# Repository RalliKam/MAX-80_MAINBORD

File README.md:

# LOBO MAX-80 · CPU Logic Board

This KiCad 10 project recreates the LOBO MAX-80 mainboard from the original schematics. The board contains the Z80B processor, main memory, serial interfaces, floppy disk controller, and video circuitry.
The work ist NOT finished!!!!

The schematic spans five sheets. The PCB layout contains **228 footprints**. Routing is still pending.

## Technical documentation

- [MAX-80 Technical Reference Manual (PDF)](Tech_Ref_Manual_Updated.pdf)
- [Appendix H – Original Schematics (PDF)](z80_Appendix_H_Schematics_Updated.pdf)
- [CPU logic board component placement diagram](CPU%20LOGIC%20Board.png)

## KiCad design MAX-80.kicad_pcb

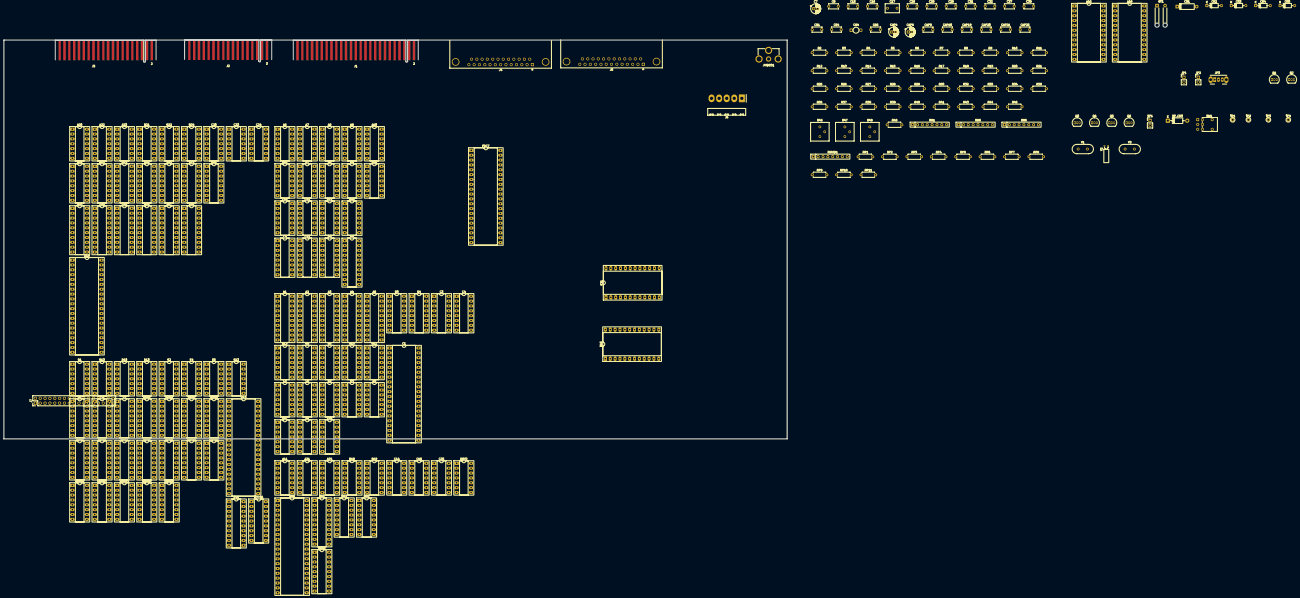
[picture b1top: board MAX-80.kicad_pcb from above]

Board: 2 copper layers, 410.0 x 208.7 mm, 228 parts (0 on the bottom side), 533 nets, no tracks yet.

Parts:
A1: 74LS688; DIP-20_W7.62mm_Socket_LongPads
A2: 74LS273; DIP-20_W7.62mm_Socket_LongPads
A3: 74LS245; DIP-20_W7.62mm_Socket_LongPads
A4, A5: 74LS244; DIP-20_W7.62mm_Socket_LongPads
A6: 74LS14; DIP-14_W7.62mm_Socket_LongPads
A7, A10: 7406; DIP-14_W7.62mm_Socket_LongPads
A8, A9, A12: 7438; DIP-14_W7.62mm_Socket_LongPads
A11, A24: 74LS393; DIP-14_W7.62mm_Socket_LongPads
A13: 74LS04; DIP-14_W7.62mm_Socket_LongPads
A16: SERIAL B; DIP-24_W15.24mm_Socket_LongPads
A18: SERIAL A; DIP-24_W15.24mm_Socket_LongPads
A20: 74LS20; DIP-14_W7.62mm_Socket_LongPads
A21: 74LS00; DIP-14_W7.62mm_Socket_LongPads
A22, A23: 74LS02; DIP-14_W7.62mm_Socket_LongPads
B1, B22: 74LS11; DIP-14_W7.62mm_Socket_LongPads
B2: 74LS157; DIP-16_W7.62mm_Socket_LongPads
B3: 74S139; DIP-16_W7.62mm_Socket_LongPads
B4: 74LS138; DIP-16_W7.62mm_Socket_LongPads
B5: 74S32; DIP-14_W7.62mm_Socket_LongPads
B6, B24: 74LS32; DIP-14_W7.62mm_Socket_LongPads
B7, B11: 74LS00; DIP-14_W7.62mm_Socket_LongPads
B8: 74LS393; DIP-14_W7.62mm_Socket_LongPads
B9, B13, B21: 74LS04; DIP-14_W7.62mm_Socket_LongPads
B10: 74LS02; DIP-14_W7.62mm_Socket_LongPads
B12: 74LS74; DIP-14_W7.62mm_Socket_LongPads
B14, B25: 74LS109; DIP-16_W7.62mm_Socket_LongPads
B15: 74LS244; DIP-20_W7.62mm_Socket_LongPads
B16: Z80 SIO/2; DIP-40_W15.24mm_Socket_LongPads
B18, B19: MC1489; DIP-14_W7.62mm_Socket_LongPads
B20: 74LS161; DIP-16_W7.62mm_Socket_LongPads
B23: 74LS273; DIP-20_W7.62mm_Socket_LongPads
BRG1: COM8116; DIP-18_W7.62mm_Socket_LongPads
BT1: 3,6 V NiCd; SolderWire-0.25sqmm_1x02_P4.2mm_D0.65mm_OD1.7mm_Relief
C1: Z80B; DIP-40_W15.24mm_Socket_LongPads
C3: 74S139; DIP-16_W7.62mm_Socket_LongPads
C4: 74LS138; DIP-16_W7.62mm_Socket_LongPads
C5: 74S32; DIP-14_W7.62mm_Socket_LongPads
C6: 74LS30; DIP-14_W7.62mm_Socket_LongPads
C7: 10 µF; CP_Radial_D5.0mm_P2.00mm
C8: 680NF; C_Disc_D5.0mm_W2.5mm_P5.00mm
C9: 74LS175; DIP-16_W7.62mm_Socket_LongPads
C10: 74LS132; DIP-14_W7.62mm_Socket_LongPads
C11, C23: 74LS00; DIP-14_W7.62mm_Socket_LongPads
C12: 74LS629; DIP-16_W7.62mm_Socket_LongPads
C14: 74LS393; DIP-14_W7.62mm_Socket_LongPads
C15, C16, C66: 100nF; C_Disc_D5.0mm_W2.5mm_P5.00mm
C17: 1 µF; C_Rect_L7.2mm_W4.5mm_P5.00mm
C19: MC1488; DIP-14_W7.62mm_Socket_LongPads
C20: 74LS02; DIP-14_W7.62mm_Socket_LongPads
C21, C22: 74LS273; DIP-20_W7.62mm_Socket_LongPads
C24: 74LS08; DIP-14_W7.62mm_Socket_LongPads
C25: 74LS04; DIP-14_W7.62mm_Socket_LongPads
C26: 200nF; C_Disc_D5.0mm_W2.5mm_P5.00mm
C28, C29: 0,01 µF; C_Disc_D5.0mm_W2.5mm_P5.00mm
C31, C32: 0,001 µF; C_Disc_D5.0mm_W2.5mm_P5.00mm
C37: 68 nF; C_Disc_D5.0mm_W2.5mm_P5.00mm
C38: 39 nF; C_Disc_D5.0mm_W2.5mm_P5.00mm
C51: 20 pF; C_Disc_D5.0mm_W2.5mm_P5.00mm
C54: 200nf; C_Disc_D5.0mm_W2.5mm_P5.00mm
C64: 5–35 pF; C_Trimmer_GKX35011_P5.00mm
CAP4: 10 µF; CP_Radial_D5.0mm_P2.00mm
CAP6: 1 µF; CP_Radial_D5.0mm_P2.00mm
CAP9: 200nF; C_Disc_D5.0mm_W2.5mm_P5.00mm
CAP10, CAP20: 390; C_Disc_D5.0mm_W2.5mm_P5.00mm
CAP19: 180; C_Disc_D5.0mm_W2.5mm_P5.00mm
CAP21: 200 pF; C_Disc_D5.0mm_W2.5mm_P5.00mm
CAP25: 430; C_Disc_D5.0mm_W2.5mm_P5.00mm
CR1: 1N34A; D_DO-7_P10.16mm_Horizontal
CR2, CR3, CR4, CR5: 1N4148; D_DO-35_SOD27_P7.62mm_Horizontal
D3: 74LS11; DIP-14_W7.62mm_Socket_LongPads
D4: 74LS20; DIP-14_W7.62mm_Socket_LongPads
D5: 74LS04; DIP-14_W7.62mm_Socket_LongPads
D6: 74LS273; DIP-20_W7.62mm_Socket_LongPads
D9: 74LS123; DIP-16_W7.62mm_Socket_LongPads
D10, D11, D12: 74LS74; DIP-14_W7.62mm_Socket_LongPads
D13: 74LS02; DIP-14_W7.62mm_Socket_LongPads
D14: Z80 PIO; DIP-40_W15.24mm_Socket_LongPads
D16: 6116; DIP-24_W15.24mm_Socket_LongPads
D17: 74LS08; DIP-14_W7.62mm_Socket_LongPads
D18: HD46505; DIP-40_W15.24mm_Socket_LongPads
D20: 74LS245; DIP-20_W7.62mm_Socket_LongPads
D23, D24, D25: 74LS157; DIP-16_W7.62mm_Socket_LongPads
DRV2: MC1488; DIP-14_W7.62mm_Socket_LongPads
E1, E13: 74LS32; DIP-14_W7.62mm_Socket_LongPads
E2, E16: 74LS74; DIP-14_W7.62mm_Socket_LongPads
E4: 74LS393; DIP-14_W7.62mm_Socket_LongPads
E5: 74LS00; DIP-14_W7.62mm_Socket_LongPads
E12: 74S472; DIP-20_W7.62mm_Socket_LongPads
E17: 74LS323; DIP-20_W7.62mm_Socket_LongPads
E20: 74LS245; DIP-20_W7.62mm_Socket_LongPads
E21: 6116; DIP-24_W15.24mm_Socket_LongPads
E23, E24, E25: 74LS157; DIP-16_W7.62mm_Socket_LongPads
F4, F5: 74LS157; DIP-16_W7.62mm_Socket_LongPads
FDC7: 8866; DIP-40_W15.24mm_Socket_LongPads
J1: Floppy 8 Zoll; Floppy_Shugart_50Pin_P2.54mm_Key4-6
J2: Floppy 5¼ Zoll; Floppy_Shugart_34Pin_P2.54mm_Key4-6
J3: Systembus; Expansion_40Pin_P2.54mm_Key4-6
J4: RS-232 A; DSUB-25_Pins_Horizontal_P2.77x2.84mm_EdgePinOffset9.90mm_Ho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
J5: RS-232 B; DSUB-25_Pins_Horizontal_P2.77x2.84mm_EdgePinOffset9.90mm_Ho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
J6: Netzteileingang (A/25); Molex_KK-396_A-41792-0005_1x05_P3.96mm_Horizontal
J7: Keyboard Interface; PinHeader_2x17_P2.54mm_Vertical
JP1: BUSRQ; PinHeader_1x02_P2.54mm_Vertical
JP2: HALT; PinHeader_1x02_P2.54mm_Vertical
JP3: SIDE / DS4; SW_Slide_SPDT_Angled_CK_OS102011MA1Q
JVIDEO1: Video · Cinch; CUI_RCJ-01X_MAX80
Q1, Q6: 2N3906; TO-92_Inline
Q2, Q3, Q4, Q5: 2N3904; TO-92_Inline
R2, R38: 5,6 kΩ; R_Axial_DIN0207_L6.3mm_D2.5mm_P7.62mm_Horizontal
R3, R14: 2,7 kΩ; R_Axial_DIN0207_L6.3mm_D2.5mm_P7.62mm_Horizontal
R4, R6, R25: 10 kΩ; R_Axial_DIN0207_L6.3mm_D2.5mm_P7.62mm_Horizontal
R5, R16, R18, R41, R43, R49: 1 kΩ; R_Axial_DIN0207_L6.3mm_D2.5mm_P7.62mm_Horizontal
R7, R8, R9, R10, R11, R12: 150 Ω; R_Axial_DIN0207_L6.3mm_D2.5mm_P7.62mm_Horizontal
R13: 1,8 kΩ; R_Axial_DIN0207_L6.3mm_D2.5mm_P7.62mm_Horizontal
R15: 75 Ω; R_Axial_DIN0207_L6.3mm_D2.5mm_P7.62mm_Horizontal
R17: 2,2 kΩ; R_Axial_DIN0207_L6.3mm_D2.5mm_P7.62mm_Horizontal
R19, R21, R32, R33, R36: 330 Ω; R_Axial_DIN0207_L6.3mm_D2.5mm_P7.62mm_Horizontal
R20: 470 Ω; R_Axial_DIN0207_L6.3mm_D2.5mm_P7.62mm_Horizontal
R26: 15 kΩ; R_Axial_DIN0207_L6.3mm_D2.5mm_P7.62mm_Horizontal
R27: 47 kΩ; R_Axial_DIN0207_L6.3mm_D2.5mm_P7.62mm_Horizontal
R28: 68 kΩ; R_Axial_DIN0207_L6.3mm_D2.5mm_P7.62mm_Horizontal
R29, R30: 56 Ω; R_Axial_DIN0207_L6.3mm_D2.5mm_P7.62mm_Horizontal
R34, R37: 4,7 kΩ; R_Axial_DIN0207_L6.3mm_D2.5mm_P7.62mm_Horizontal
R35: 3 kΩ; R_Axial_DIN0207_L6.3mm_D2.5mm_P7.62mm_Horizontal
R39, R40, R44: 200 Ω; R_Axial_DIN0207_L6.3mm_D2.5mm_P7.62mm_Horizontal
R45: 22 Ω; R_Axial_DIN0207_L6.3mm_D2.5mm_P7.62mm_Horizontal
R46, R47, R48: 5 kΩ; Potentiometer_Bourns_3386P_Vertical
RAM1, RAM2, RAM3, RAM4, RAM5, RAM6, RAM7, RAM8, RAM9, RAM10, RAM11, RAM12, RAM13, RAM14, RAM15, RAM16: 4164; DIP-16_W7.62mm_Socket_LongPads
RN1: 2,7 kΩ; R_Array_SIP8
RN5: 1 kΩ; R_Array_SIP8
RN6: 150 Ω; R_Array_SIP8
RNVID1: 2,7 kΩ; R_Array_SIP8
RP1, RP2, RP3, RP4, RP5, RP6, RP7, RP8, RP9, RP10, RP11: 10 kΩ; R_Axial_DIN0207_L6.3mm_D2.5mm_P7.62mm_Horizontal
RTC16: MSM5832; DIP-18_W7.62mm_Socket_LongPads
SP1: Lautsprecher; PinHeader_1x02_P2.54mm_Vertical
SP_CR3: 1N4003; D_DO-41_SOD81_P10.16mm_Horizontal
SW1: CLOCK SET; Clock_Set_800UDP8P1A1M6
TP1: TP; TestPoint_THTPad_D2.0mm_Drill1.0mm
TP2, TP3, TP4: Prüfpunkt; TestPoint_THTPad_D2.0mm_Drill1.0mm
Y1: 8,00 MHz; Crystal_HC49-U_Vertical
Y2: 32,768 kHz; Crystal_C26-LF_D2.1mm_L6.5mm_Horizontal
Y3: 15,2 MHz; Crystal_HC49-U_Vertical

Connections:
5SEC: A7.11, B7.1, B7.8, B7.12, B15.6 (1A3)
500KC: A11.8 (D), C14.1 (CLK)
+5V: A1.20 (VCC), A2.20 (VCC), A3.20 (VCC), A4.20 (VCC), A5.20 (VCC), A6.14 (+5V), A7.14 (+5V), A8.14 (+5V), A9.14 (+5V), A10.14 (+5V), A11.14 (+5V), A12.14 (+5V), A13.14 (VCC), A20.14 (+5V), A21.14 (+5V), A22.14 (+5V), A23.14 (+5V), A24.14 (+5V), B1.14 (+5V), B2.16 (+5V), B3.16 (VCC), B4.16 (VCC), B5.14 (VCC), B6.14 (VCC), B7.14 (+5V), B8.14 (+5V), B9.14 (+5V), B10.14 (VCC), B11.14 (VCC), B12.14 (+5V), B13.14 (VCC), B14.16 (+5V), B15.20 (+5V), B16.6 (IEI), B16.8 (~M1), B16.9 (VCC), B18.14 (+5V), B19.14 (+5V), B20.16 (+5V), B21.14 (+5V), B22.14 (+5V), B23.20 (+5V), B24.14 (+5V), B25.16 (+5V), BRG1.2 (VCC), C1.11 (VCC), C3.16 (VCC), C4.16 (VCC), C5.14 (VCC), C6.14 (VCC), C9.16 (+5V), C10.14 (+5V), C11.14 (+5V), C12.3 (RNG), C12.14 (RNG), C12.15 (+5V), C12.16 (+5V), C14.14 (+5V), C17.1, C20.14 (+5V), C21.20 (+5V), C22.20 (+5V), C23.14 (+5V), C24.14 (+5V), C25.14 (+5V), D3.14 (VCC), D4.14 (VCC), D5.14 (VCC), D6.20 (+5V), D9.16 (+5V), D10.14 (VCC), D11.14 (+5V), D12.14 (+5V), D13.14 (VCC), D14.26 (VCC), D14.37 (~M1), D16.24 (VCC), D17.14 (VCC), D18.2 (~RES), D18.20 (VCC), D20.20 (+5V), D23.16 (+5V), D24.16 (+5V), D25.16 (+5V), E1.14 (VCC), E2.14 (+5V), E4.14 (+5V), E5.14 (+5V), E12.20 (+5V), E13.14 (VCC), E16.14 (VCC), E17.20 (+5V), E20.20 (+5V), E21.24 (VCC), E23.16 (+5V), E24.16 (+5V), E25.16 (+5V), F4.16 (+5V), F5.16 (+5V), FDC7.21 (VCC), J6.1, J6.5, J7.28, J7.29, Q4.3, Q5.3, R2.1, R3.1, R4.1, R14.1, R36.2, R38.2, R41.1, R45.1, R46.3, R47.1, R48.1, R49.1, RAM1.8 (VCC), RAM2.8 (VCC), RAM3.8 (VCC), RAM4.8 (VCC), RAM5.8 (VCC), RAM6.8 (VCC), RAM7.8 (VCC), RAM8.8 (VCC), RAM9.8 (VCC), RAM10.8 (VCC), RAM11.8 (VCC), RAM12.8 (VCC), RAM13.8 (VCC), RAM14.8 (VCC), RAM15.8 (VCC), RAM16.8 (VCC), RN1.1, RN5.1, RN6.1, RNVID1.1, RP1.1, RP2.1, RP3.1, RP4.1, RP5.1, RP6.1, RP7.1, RP8.1, RP9.1, RP10.1, RP11.1, SP1.1, SP_CR3.1
+12V: BRG1.9 (VDD), C19.14 (VCC), DRV2.14 (VCC), J6.3, R6.1, R8.2, R10.2
-12V: C19.1 (VEE), DRV2.1 (VEE), J6.4, R9.2, R11.2
/1 · CPU und Systembus/J3_18: A4.3 (2Y4), J3.18
/1 · CPU und Systembus/XA0: A5.3 (2Y4), J3.26
/1 · CPU und Systembus/XA1: A5.5 (2Y3), J3.28
/1 · CPU und Systembus/XA2: A5.7 (2Y2), J3.39
/1 · CPU und Systembus/XA3: A5.9 (2Y1), J3.33
/1 · CPU und Systembus/XA4: A5.12 (1Y4), J3.32
/1 · CPU und Systembus/XA5: A5.14 (1Y3), J3.36
/1 · CPU und Systembus/XA6: A5.16 (1Y2), J3.37
/1 · CPU und Systembus/XA7: A5.18 (1Y1), J3.35
/1 · CPU und Systembus/XD0: A3.11 (B8), J3.29
/1 · CPU und Systembus/XD1: A3.12 (B7), J3.21
/1 · CPU und Systembus/XD2: A3.13 (B6), J3.31
/1 · CPU und Systembus/XD3: A3.14 (B5), J3.25
/1 · CPU und Systembus/XD4: A3.15 (B4), J3.17
/1 · CPU und Systembus/XD5: A3.16 (B3), J3.27
/1 · CPU und Systembus/XD6: A3.17 (B2), J3.23
/1 · CPU und Systembus/XD7: A3.18 (B1), J3.19
/1 · CPU und Systembus/XΦZ: A4.5 (2Y3), J3.6
/1 · CPU und Systembus/~WAIT: E1.12, J3.34, RN1.8
/1 · CPU und Systembus/~XINTAK: A4.7 (2Y2), CR1.1, J3.13
/1 · CPU und Systembus/~XINT: D3.9, J3.22, RN1.7
/1 · CPU und Systembus/~XIN: A4.14 (1Y3), J3.20
/1 · CPU und Systembus/~XIORQ: A4.12 (1Y4), J3.10
/1 · CPU und Systembus/~XM1: A4.9 (2Y1), J3.9
/1 · CPU und Systembus/~XNMI: E1.1, J3.24, RN1.4
/1 · CPU und Systembus/~XOUT: A4.16 (1Y2), J3.11
/1 · CPU und Systembus/~XSYSRES: A4.18 (1Y1), J3.1
/4 · Floppycontroller und Laufwerke/1M: A11.9 (C), B11.12, B12.3 (CLK)
/4 · Floppycontroller und Laufwerke/2M: A11.10 (B), B11.9
A0: A5.17 (2A4), C1.30 (A0), D14.5 (C/~D), D18.24 (RS), D23.11 (A2), E12.1 (A0), E23.14 (A3), F5.2 (1A), FDC7.5 (A0), J7.2
A1: A5.15 (2A3), C1.31 (A1), D14.6 (B/~A), D23.14 (A3), E12.2, E23.11 (A2), F5.5 (2A), FDC7.6 (A1), J7.3
A2: A5.13 (2A2), B4.1 (A), C1.32 (A2), C3.14 (A), C4.1 (A), D24.2 (A0), E12.3, E23.5 (A1), F5.11 (3A), J7.4
A3: A5.11 (2A1), B4.2 (B), C1.33 (A3), C3.13 (B), C4.2 (B), D24.5 (A1), E12.4, E24.14 (A3), F5.14 (4A), J7.5
A4: A5.8 (1A4), B4.3 (C), C1.34 (A4), C4.3 (C), D4.13, D24.11 (A2), E12.5, E24.11 (A2), F4.2 (1A), J7.6
A5: A5.6 (1A3), B10.5, C1.35 (A5), D4.5, D24.14 (A3), E12.16, E24.5 (A1), F4.5 (2A), J7.7
A6: A5.4 (1A2), C1.36 (A6), D4.4, D4.10, D25.2 (A0), E12.17, E24.2 (A0), F4.11 (3A), J7.8
A7: A5.2 (1A1), C1.37 (A7), D4.1, D4.2, D4.9, D25.5 (A1), E5.12, E12.18, E25.14 (A3), J7.9
A8: B3.14 (A), C1.38 (A8), D25.11 (A2), E12.19 (A8), E25.11 (A2), F5.3 (1B)
A9: B3.13 (B), C1.39 (A9), E25.5 (A1), F5.6 (2B)
A10: B3.2 (A), C1.40 (A10), C25.5, F5.10 (3B)
A11: B3.3 (B), C1.1 (A11), F5.13 (4B)
A12: A1.11 (P4), C1.2 (A12), F4.3 (1B)
A13: A1.13 (P5), C1.3 (A13), F4.6 (2B)
A14: A1.15 (P6), C1.4 (A14), F4.10 (3B)
A15: A1.17 (P7), B2.1 (SEL), C1.5 (A15)
BLOCK: C6.8, E1.5
D0: A2.18 (D7), A3.9 (A8), B16.40 (D0), BRG1.4 (D0B), BRG1.16 (D0A), C1.14 (D0), CR1.2, D6.3 (D0), D14.19 (D0), D18.33 (D0), D20.9 (A8), E12.6 (D0), E20.2 (A1), FDC7.7 (DAL0), J7.11, RAM8.2 (DI), RAM8.14 (DO), RAM16.2 (DI), RAM16.14 (DO)
D1: A2.17 (D6), A3.8 (A7), B16.1 (D1), BRG1.5 (D1B), BRG1.15 (D1A), C1.15 (D1), D6.18 (D7), D14.20, D18.32 (D1), D20.8 (A7), E12.7, E20.3 (A2), FDC7.8 (DAL1), J7.12, RAM7.2 (DI), RAM7.14 (DO), RAM15.2 (DI), RAM15.14 (DO), RNVID1.7
D2: A2.14 (D5), A3.7 (A6), B16.39 (D2), BRG1.6 (D2B), BRG1.14 (D2A), C1.12 (D2), D6.4 (D1), D13.3, D14.1, D18.31 (D2), D20.7 (A6), E12.8, E20.4 (A3), FDC7.9 (DAL2), J7.13, RAM6.2 (DI), RAM6.14 (DO), RAM14.2 (DI), RAM14.14 (DO), RNVID1.6
D3: A2.13 (D4), A3.6 (A5), B16.2 (D3), BRG1.7 (D3B), BRG1.13 (D3A), C1.8 (D3), D6.17 (D6), D14.40, D18.30 (D3), D20.6 (A5), E12.9, E20.5 (A4), FDC7.10 (DAL3), J7.14, RAM5.2 (DI), RAM5.14 (DO), RAM13.2 (DI), RAM13.14 (DO), RNVID1.5
D4: A2.8 (D3), A3.5 (A4), B15.9 (2Y1), B15.18 (1Y1), B16.38 (D4), C1.7 (D4), D6.7 (D2), D14.39, D18.29 (D4), D20.5 (A4), E12.11, E20.6 (A5), FDC7.11 (DAL4), J7.15, RAM4.2 (DI), RAM4.14 (DO), RAM12.2 (DI), RAM12.14 (DO), RNVID1.4
D5: A2.7 (D2), A3.4 (A3), B15.7 (2Y2), B15.16 (1Y2), B16.3 (D5), C1.9 (D5), D6.14 (D5), D14.38, D18.28 (D5), D20.4 (A3), E12.12, E20.7 (A6), FDC7.12 (DAL5), J7.16, RAM3.2 (DI), RAM3.14 (DO), RAM11.2 (DI), RAM11.14 (DO), RNVID1.3
D6: A2.4 (D1), A3.3 (A2), B15.5 (2Y3), B15.14 (1Y3), B16.37 (D6), C1.10 (D6), D6.8 (D3), D14.3, D18.27 (D6), D20.3 (A2), E12.13, E20.8 (A7), FDC7.13 (DAL6), J7.17, RAM2.2 (DI), RAM2.14 (DO), RAM10.2 (DI), RAM10.14 (DO), RNVID1.2
D7: A2.3 (D0), A3.2 (A1), B15.3 (2Y4), B15.12 (1Y4), B16.4 (D7), C1.13 (D7), D6.13 (D4), D14.2 (D7), D18.26 (D7), D20.2 (A1), D23.5 (A1), E12.14 (D7), E20.9 (A8), FDC7.14 (DAL7), J7.18, RAM1.2 (DI), RAM1.14 (DO), RAM9.2 (DI), RAM9.14 (DO), RNVID1.8
DNM: B7.4, D6.12 (Q4), E1.2
DRQ: E13.13, FDC7.38 (DRQ), J7.19
DSPTMG: B15.4 (1A2), C21.18 (D7), D18.18 (DISPTMG)
GND: A1.10 (GND), A2.10 (GND), A3.10 (GND), A4.1 (~1G), A4.10 (GND), A4.19 (~2G), A5.1 (~1G), A5.10 (GND), A5.19 (~2G), A6.7 (GND), A7.7 (GND), A8.7 (GND), A9.7 (GND), A10.7 (GND), A11.2 (CLR), A11.7 (GND), A11.12 (CLR), A12.7 (GND), A13.7 (GND), A20.7 (GND), A21.7 (GND), A22.7 (GND), A23.7 (GND), A24.7 (GND), B1.7 (GND), B2.8 (GND), B2.15 (~EN), B3.8 (GND), B4.8 (GND), B5.7 (GND), B6.7 (GND), B7.7 (GND), B8.7 (GND), B9.7 (GND), B10.7 (GND), B11.7 (GND), B12.7 (GND), B13.7 (GND), B14.2 (J), B14.8 (GND), B14.13 (~K), B15.10 (GND), B16.31 (VSS), B16.35 (~CE), B18.7 (GND), B19.7 (GND), B20.3 (A), B20.4 (B), B20.5 (C), B20.8 (GND), B21.7 (GND), B22.7 (GND), B23.10 (GND), B24.7 (GND), B25.8 (GND), B25.13 (~K), BRG1.11 (VSS), BT1.2, C1.29 (GND), C3.8 (GND), C4.8 (GND), C5.7 (GND), C6.7 (GND), C7.2, C8.2, C9.8 (GND), C10.7 (GND), C11.7 (GND), C12.8 (GND), C12.9 (GND), C14.2 (CLR), C14.7 (GND), C14.12 (CLR), C15.2, C16.2, C19.7 (GND), C20.7 (GND), C21.10 (GND), C22.10 (GND), C23.7 (GND), C24.7 (GND), C25.7 (GND), C26.2, C31.2, C32.2, C51.2, C64.2, CAP4.2, CAP6.2, CAP21.2, CAP25.2, D3.7 (GND), D4.7 (GND), D5.7 (GND), D6.10 (GND), D9.1 (A), D9.8 (GND), D9.9 (A), D10.7 (GND), D11.7 (GND), D12.7 (GND), D13.7 (GND), D14.4 (~CE), D14.11 (VSS), D14.24 (IEI), D16.12 (GND), D17.7 (GND), D18.1 (VSS), D18.3 (LPSTB), D18.22 (R/~W), D18.25 (~CS), D20.10 (GND), D23.8 (GND), D23.15 (~G), D24.8 (GND), D24.15 (~G), D25.8 (GND), D25.15 (~G), DRV2.7 (GND), E1.7 (GND), E2.7 (GND), E4.2 (CLR), E4.7 (GND), E4.12 (CLR), E5.7 (GND), E12.10 (GND), E13.7 (GND), E16.7 (GND), E17.10 (GND), E17.11 (SR), E20.10 (GND), E21.12 (GND), E23.8 (GND), E23.15 (~G), E24.8 (GND), E24.15 (~G), E25.8 (GND), E25.15 (~G), F4.8 (GND), F4.15 (~G), F5.8 (GND), F5.15 (~G), FDC7.3 (~CS), FDC7.20 (VSS), J1.1, J1.3, J1.5, J1.7, J1.9, J1.11, J1.13, J1.15, J1.17, J1.19, J1.21, J1.23, J1.25, J1.27, J1.29, J1.31, J1.33, J1.35, J1.37, J1.39, J1.41, J1.43, J1.45, J1.47, J1.49, J2.1, J2.3, J2.5, J2.7, J2.9, J2.11, J2.13, J2.15, J2.17, J2.19, J2.21, J2.23, J2.25, J2.27, J2.29, J2.31, J2.33, J3.3, J3.7, J4.1, J4.7, J5.1, J5.7, J6.2, J7.1, J7.10, JP1.2, JVIDEO1.2, Q2.1, Q3.1, Q6.3, R12.2, R17.1, R18.2, R21.2, R34.2, R35.2, R47.3, R48.3, RAM1.16 (VSS), RAM2.16 (VSS), RAM3.16 (VSS), RAM4.16 (VSS), RAM5.16 (VSS), RAM6.16 (VSS), RAM7.16 (VSS), RAM8.16 (VSS), RAM9.16 (VSS), RAM10.16 (VSS), RAM11.16 (VSS), RAM12.16 (VSS), RAM13.16 (VSS), RAM14.16 (VSS), RAM15.16 (VSS), RAM16.16 (VSS), RTC16.13 (GND), RTC16.14 (TEST)
INTRQ: FDC7.39 (INTRQ), J7.27
unnamed: A1.12 (Q4), A2.9 (Q3)
unnamed: A1.14 (Q5), A2.6 (Q2)
unnamed: A1.16 (Q6), A2.5 (Q1)
unnamed: A1.18 (Q7), A2.2 (Q0)
unnamed: A2.11 (CLK), C3.9 (~Y3)
unnamed: A2.15 (Q5), C3.3 (B)
unnamed: A2.19 (Q7), B5.5
unnamed: A3.1 (DIR), A4.6 (1A3), B6.11
unnamed: A3.19 (~G), A4.8 (1A4), B6.2, B6.5, B6.13, B11.1, C1.20 (~IORQ), E1.13
unnamed: A4.4 (1A2), B6.3
unnamed: A4.11 (2A1), B6.4, C1.27 (~M1)
unnamed: A4.13 (2A2), B6.6
unnamed: A6.1, J1.44, J2.28, RN6.2
unnamed: A6.2, A6.13
unnamed: A6.3, J1.42, J2.26, RN6.3
unnamed: A6.4, A6.11
unnamed: A6.5, J1.46, J2.30, RN6.5
unnamed: A6.8, B9.3
unnamed: A6.9, J1.20, J2.8, RN6.6
unnamed: A7.2, J2.20
unnamed: A7.4, J2.22
unnamed: A7.6, J2.18
unnamed: A7.8, CAP9.2
unnamed: A7.9, C11.6
unnamed: A7.10, J2.16
unnamed: A7.12, JP3.1
unnamed: A8.2, A8.5, A8.10, A8.13, B9.6
unnamed: A8.3, J2.6, JP3.3
unnamed: A8.6, J2.10
unnamed: A8.8, J2.12
unnamed: A8.11, J2.14
unnamed: A9.3, J1.32
unnamed: A9.6, J1.26
unnamed: A9.8, J1.28
unnamed: A9.11, J1.30
unnamed: A7.3, A10.1, B9.2
unnamed: A10.2, J1.38
unnamed: A10.4, J1.36
unnamed: A10.6, J1.34
unnamed: A10.8, J1.2
unnamed: A10.10, J1.14
unnamed: A10.12, J1.18
unnamed: A9.2, A9.5, A9.10, A9.13, A10.13, D17.8
unnamed: A11.6 (D), B25.12 (CLK)
unnamed: A11.13 (CLK), A13.4, Y1.2
unnamed: A12.3, J2.24
unnamed: A12.8, CAP10.2
unnamed: A12.11, J1.40
unnamed: A13.1, R5.1, Y1.1
unnamed: A13.2, A13.3, R5.2
unnamed: A13.6, E13.9
unnamed: A13.8, C54.1, D5.11, R43.1
unnamed: A13.12, A23.5
unnamed: A16.1, R10.1
unnamed: A16.2, DRV2.11
unnamed: A16.3, DRV2.3
unnamed: A16.4, DRV2.6
unnamed: A16.5, DRV2.8
unnamed: A16.10, R11.1
unnamed: A16.15, J5.6
unnamed: A16.16, J5.8
unnamed: A16.17, J5.5
unnamed: A16.18, J5.17
unnamed: A16.19, J5.3
unnamed: A16.20, J5.20
unnamed: A16.21, J5.4
unnamed: A16.22, J5.24
unnamed: A16.23, J5.2
unnamed: A18.1, R8.1
unnamed: A18.2, C19.11
unnamed: A18.3, C19.3
unnamed: A18.4, C19.6
unnamed: A18.5, C19.8
unnamed: A18.10, R9.1
unnamed: A18.15, J4.6
unnamed: A18.16, J4.8
unnamed: A18.17, J4.5
unnamed: A18.18, J4.17
unnamed: A18.19, J4.3
unnamed: A18.20, J4.20
unnamed: A18.21, J4.4
unnamed: A18.22, J4.24
unnamed: A18.23, J4.2
unnamed: A20.8, B21.1
unnamed: A20.10, B21.4
unnamed: A21.4, B24.10, C20.2, C24.11
unnamed: A21.5, B24.5, C20.11, C24.3
unnamed: A21.9, A21.12, C25.2
unnamed: A21.11, C17.2, SP1.2, SP_CR3.2
unnamed: A22.1, R13.1
unnamed: A22.2, A22.10, C24.9
unnamed: A23.10, C10.10
unnamed: A24.5 (C), C25.1
unnamed: A21.8, A24.1 (CLK)
unnamed: A21.3, A24.2 (CLR)
unnamed: A22.8, A24.9 (C)
unnamed: A24.13 (CLK), C24.8
unnamed: A13.10, A22.9, A24.12 (CLR)
unnamed: B1.6, D5.9, E13.5
unnamed: B2.11 (A0), D14.10 (4)
unnamed: B2.14 (A1), D14.9 (5)
unnamed: B2.10 (B0), D14.8 (6)
unnamed: B2.13 (B1), D14.7
unnamed: B1.9, B2.9 (Y0)
unnamed: B1.4, B1.5, B2.12 (Y1)
unnamed: B3.4 (~Y0), C3.1 (~G)
unnamed: B3.5 (~Y1), B5.1
unnamed: B3.6 (~Y2), C5.1
unnamed: B3.12 (~Y0), C5.2
unnamed: B3.9 (~Y3), B5.2
unnamed: B4.4 (~G2A), C4.4 (~G2A), C5.6, C5.9
unnamed: B5.6, B5.9
unnamed: B5.12, C5.3
unnamed: B7.3, B8.1 (CLK)
unnamed: B7.5, E13.11
unnamed: B7.9, B8.8 (D)
unnamed: B7.11, B9.5, C10.2
unnamed: B7.10, B8.9 (C)
unnamed: B8.6 (D), B8.13 (CLK)
unnamed: B8.2 (CLR), B8.12 (CLR), D13.1
unnamed: B10.4, D4.12
unnamed: B10.8, C10.11
unnamed: B9.1, B10.10, R19.2
unnamed: B5.3, B11.2, C5.4, C5.12
unnamed: B11.3, D17.12
unnamed: B11.10, B11.11
unnamed: B12.2 (D), C11.4, C12.11 (~EN), D6.15 (Q5), D17.10
unnamed: A12.10, B7.13, B11.13, B12.6 (~Q), C12.6 (~EN)
unnamed: B12.11 (CLK), C11.8, D13.12
unnamed: B12.8 (~Q), B12.12 (D)
unnamed: B12.9 (Q), D10.11 (CLK), D13.8
unnamed: B13.8, R30.1
unnamed: B14.6 (Q), B15.8 (1A4)
unnamed: B16.13 (RxCA), B19.6 (OUT2)
unnamed: B16.28 (RxCB), B18.6 (OUT2)
unnamed: B16.12 (RxDA), B19.3 (OUT1)
unnamed: B16.29 (RxDB), B18.3 (OUT1)
unnamed: B16.14 (TxCA), BRG1.3 (QA), C19.2
unnamed: B16.27 (TxCB), BRG1.17 (QB), DRV2.2
unnamed: B16.15 (TxDA), C19.12, C19.13
unnamed: B16.26 (TxDB), DRV2.12, DRV2.13
unnamed: B16.18 (~CTSA), B19.8 (OUT3)
unnamed: B16.23 (~CTSB), B18.11 (OUT3)
unnamed: B16.19 (~DCDA), B19.11 (OUT4)
unnamed: B16.22 (~DCDB), B18.8 (OUT4)
unnamed: B16.16 (~DTRA), C19.9, C19.10
unnamed: B16.25 (~DTRB), DRV2.9, DRV2.10
unnamed: B16.36 (~IORQ), D17.3
unnamed: B16.17 (~RTSA), C19.4, C19.5
unnamed: B16.24 (~RTSB), DRV2.4, DRV2.5
unnamed: A16.6, B18.1 (IN1)
unnamed: A16.7, B18.4 (IN2)
unnamed: A16.8, B18.13 (IN3)
unnamed: A16.9, B18.10 (IN4)
unnamed: A18.6, B19.1 (IN1)
unnamed: A18.7, B19.4 (IN2)
unnamed: A18.8, B19.10 (IN3)
unnamed: A18.9, B19.13 (IN4)
unnamed: B20.2 (CLK), B23.11 (CLK), B25.4 (CLK), C25.8, E17.12 (CLK), Y3.1
unnamed: B20.6 (D), B24.1, E13.8
unnamed: B20.14 (QA), B22.9, B24.2
unnamed: A23.6, B20.13 (QB), B22.10
unnamed: B20.12 (QC), B21.13, B22.11, C10.9, D18.21 (CLK)
unnamed: B20.15 (RCO), B21.5, B22.4
unnamed: B20.9 (~LOAD), B21.6
unnamed: B21.2, B24.13
unnamed: A22.4, B23.3 (D0)
unnamed: A13.13, B23.2 (Q0), C20.5, C20.9, D23.1 (SEL), D24.1 (SEL), D25.1 (SEL), E23.1 (SEL), E24.1 (SEL), E25.1 (SEL)
unnamed: A22.5, B22.8, B23.7 (D2)
unnamed: B23.6 (Q2), B23.8 (D3)
unnamed: B21.3, B22.13, B23.9 (Q3)
unnamed: A23.12, B23.17 (D6), B24.11
unnamed: A23.13, B23.18 (D7)
unnamed: A23.11, B23.14 (D5), B23.19 (Q7)
unnamed: A23.2, B23.5 (Q1), B23.13 (D4)
unnamed: A23.3, B23.12 (Q4)
unnamed: B24.4, B24.9, C24.6
unnamed: B22.12, B25.2 (J)
unnamed: A20.4, B25.6 (Q)
unnamed: A20.12, A21.6, B22.1, B25.1 (~CLR)
unnamed: A20.13, A23.8, B25.7 (~Q), C20.3, C20.12
unnamed: B25.10 (Q), C66.2
unnamed: B13.10, BRG1.8 (A)
unnamed: B13.12, BRG1.12 (B)
unnamed: BRG1.1 (XT1), C15.1, R29.2
unnamed: BRG1.18 (XT2), C16.1, R30.2
unnamed: BT1.1, R7.2
unnamed: C1.6 (CLK), D5.10, Q1.3
unnamed: C1.25 (~BUSRQ), JP1.1, RN1.2
unnamed: C1.18 (~HALT), JP2.2
unnamed: C1.16 (~INT), D3.8
unnamed: C1.17 (~NMI), D3.6
unnamed: C1.24 (~WAIT), E1.10, E16.6 (~Q)
unnamed: B6.1, B10.6, C1.22 (~WR), C4.5 (~G2B)
unnamed: B5.4, C3.4 (~Y0)
unnamed: C3.15 (~G), C5.11
unnamed: C5.5, D4.6
unnamed: C5.8, C6.3
unnamed: C5.13, D4.8
unnamed: C7.1, Q2.2, R2.2, R18.1
unnamed: C9.9 (CLK), FDC7.31 (WD)
unnamed: B10.2, C9.4 (D0), FDC7.17 (EARLY)
unnamed: B10.3, C9.5 (D1), FDC7.18 (LATE)
unnamed: B10.1, C9.12 (D2)
unnamed: B10.9, C9.2 (Q0)
unnamed: C8.1, C9.1 (~CLR), R19.1
unnamed: C9.6 (~Q1), R32.1
unnamed: C9.11 (~Q2), R33.1
unnamed: C10.1, J1.22, RN6.4
unnamed: C10.8, C24.5
unnamed: C10.12, CAP25.1, R32.2
unnamed: C10.13, C26.1, R33.2
unnamed: C12.4 (CX), CAP19.1
unnamed: C12.5 (CX), CAP19.2
unnamed: C12.2 (FC), C28.1, R25.2, R27.1
unnamed: C11.9, C12.7 (Y)
unnamed: C12.12 (CX), CAP20.1
unnamed: C12.13 (CX), CAP20.2
unnamed: C12.1 (FC), C29.1, R26.2, R28.1
unnamed: C11.10, C12.10 (Y)
unnamed: C14.6 (D), C14.13 (CLK)
unnamed: C20.1, C20.6
unnamed: C20.8, C20.13
unnamed: A20.1, A20.2, A22.6, B21.12, C21.11 (CLK), C22.11 (CLK)
unnamed: C21.3 (D0), D18.35 (RA3)
unnamed: C21.4 (D1), D18.36 (RA2)
unnamed: C21.7 (D2), D18.37 (RA1)
unnamed: C21.8 (D3), D18.38 (RA0)
unnamed: C21.2 (Q0), C23.1, C23.5
unnamed: C21.5 (Q1), E23.6 (B1)
unnamed: C21.6 (Q2), E23.10 (B2)
unnamed: C21.9 (Q3), E23.13 (B3)
unnamed: B22.5, C21.19 (Q7)
unnamed: C21.1 (~CLR), C23.6, CAP21.1
unnamed: C22.3 (D0), D16.17 (D7), D20.18 (B1)
unnamed: C22.4 (D1), D16.16 (D6), D20.17 (B2)
unnamed: C22.7 (D2), D16.15 (D5), D20.16 (B3)
unnamed: C22.8 (D3), D16.9 (D0), D20.11 (B8)
unnamed: C22.13 (D4), D16.11 (D2), D20.13 (B6)
unnamed: C22.14 (D5), D16.13 (D3), D20.14 (B5)
unnamed: C22.17 (D6), D16.14 (D4), D20.15 (B4)
unnamed: C22.18 (D7), D16.10 (D1), D20.12 (B7)
unnamed: C22.2 (Q0), C23.10
unnamed: C22.5 (Q1), C23.2, C25.3, E25.6 (B1)
unnamed: C22.6 (Q2), E25.10 (B2)
unnamed: C22.9 (Q3), E24.13 (B3)
unnamed: C22.12 (Q4), E24.6 (B1)
unnamed: C22.15 (Q5), E24.3 (B0)
unnamed: C22.16 (Q6), E25.13 (B3)
unnamed: C22.19 (Q7), E24.10 (B2)
unnamed: C23.3, C23.12
unnamed: C23.4, C23.9, C25.4
unnamed: C23.8, C23.13
unnamed: C25.9, C25.10, R20.2
unnamed: C25.11, R20.1, Y3.2
unnamed: C25.13, C66.1, R21.1
unnamed: C28.2, C32.1, R35.1
unnamed: C29.2, C31.1, R34.1
unnamed: C54.2, Q1.2, R43.2, R44.2
unnamed: CAP6.1, Q6.2, R14.2, R17.2
unnamed: CR2.1, CR3.2, R25.1
unnamed: CR2.2, CR4.2, R40.2, R41.2
unnamed: CR3.1, CR5.1, R39.2
unnamed: CR4.1, CR5.2, R26.1
unnamed: D3.4, E1.3
unnamed: D3.5, JP2.1, RN1.6
unnamed: D5.1, D5.12
unnamed: D5.2, D5.3
unnamed: D5.4, D5.5
unnamed: D5.8, E13.2
unnamed: A8.4, A9.4, D6.2 (Q0)
unnamed: A8.12, A9.12, D6.5 (Q1)
unnamed: A7.13, A10.11, D6.6 (Q2)
unnamed: A8.1, A9.1, D6.16 (Q6)
unnamed: A8.9, A9.9, D6.19 (Q7)
unnamed: C38.1, D9.14 (C)
unnamed: A12.4, A12.5, D9.13 (Q)
unnamed: C38.2, D9.15 (RC), R38.1
unnamed: D9.4 (~Q), FDC7.27 (~RAWRD)
unnamed: C37.1, D9.6 (C)
unnamed: A12.6, C37.2, CAP9.1, CAP10.1, D9.7 (RC), R37.1
unnamed: B13.2, D10.3 (CLK), E2.12 (D), E2.13 (~CL)
unnamed: B11.6, D10.1 (~CLR), D10.2 (D)
unnamed: D5.13, D10.5 (Q), E2.1 (~CL), E2.2 (D)
unnamed: D10.6 (~Q), RAM1.4 (~RAS), RAM2.4 (~RAS), RAM3.4 (~RAS), RAM4.4 (~RAS), RAM5.4 (~RAS), RAM6.4 (~RAS), RAM7.4 (~RAS), RAM8.4 (~RAS), RAM9.4 (~RAS), RAM10.4 (~RAS), RAM11.4 (~RAS), RAM12.4 (~RAS), RAM13.4 (~RAS), RAM14.4 (~RAS), RAM15.4 (~RAS), RAM16.4 (~RAS)
unnamed: C11.5, D6.9 (Q3), D10.12 (D)
unnamed: D10.9 (Q), D13.9
unnamed: A12.9, D10.8 (~Q), FDC7.37 (~DDEN)
unnamed: D9.12 (~Q), D11.3 (CLK), TP3.1 (~_1)
unnamed: C11.13, D11.5 (Q), R40.1
unnamed: D11.1 (~CLR), D11.13 (~CLR), D12.5 (Q)
unnamed: D11.11 (CLK), D12.11 (CLK), D13.13, TP2.1 (~_1)
unnamed: C11.12, D11.9 (Q)
unnamed: D11.8 (~Q), R39.1
unnamed: A6.6, D9.2 (B), D9.10 (B), D12.3 (CLK), TP4.1 (~_1)
unnamed: C11.11, D12.1 (~CLR)
unnamed: D12.8 (~Q), D12.12 (D), FDC7.26 (RCLK)
unnamed: D13.10, D13.11
unnamed: D14.31 (4), RP7.2, SW1.3
unnamed: D14.33 (6), RP5.2, SW1.1
unnamed: D14.16 (~ASTB), D14.17 (~BSTB)
unnamed: D14.36 (~IORQ), D17.6
unnamed: D16.8 (A0), D23.7 (Y1)
unnamed: D16.7 (A1), D23.9 (Y2)
unnamed: D16.6 (A2), D23.12 (Y3)
unnamed: D16.5 (A3), D24.4 (Y0)
unnamed: D16.4 (A4), D24.7 (Y1)
unnamed: D16.3 (A5), D24.9 (Y2)
unnamed: D16.2 (A6), D24.12 (Y3)
unnamed: D16.1 (A7), D25.4 (Y0)
unnamed: D16.23 (A8), D25.7 (Y1)
unnamed: D16.22 (A9), D25.9 (Y2)
unnamed: D16.19 (A10), D25.12 (Y3)
unnamed: C20.4, D16.18 (~CE)
unnamed: A23.4, D16.20 (~OE), E21.20 (~OE)
unnamed: A20.6, C24.4, D16.21 (~WE), E21.21 (~WE)
unnamed: B21.8, D18.23 (E)
unnamed: A22.3, C24.10, D18.39 (HSYNC), E13.10
unnamed: D18.4 (MA0), D23.6 (B1)
unnamed: D18.5 (MA1), D23.10 (B2)
unnamed: D18.6 (MA2), D23.13 (B3)
unnamed: D18.7 (MA3), D24.3 (B0)
unnamed: D18.8 (MA4), D24.6 (B1)
unnamed: D18.9 (MA5), D24.10 (B2)
unnamed: D18.10 (MA6), D24.13 (B3)
unnamed: D18.11 (MA7), D25.3 (B0)
unnamed: D18.12 (MA8), D25.6 (B1)
unnamed: D18.13 (MA9), D25.10 (B2)
unnamed: D18.14 (MA10), D25.13 (B3)
unnamed: A13.11, D18.40 (VSYNC)
unnamed: B24.8, D20.19 (~G)
unnamed: C25.6, D25.14 (A3)
unnamed: B11.5, E2.5 (Q)
unnamed: E1.4, E2.8 (~Q)
unnamed: E4.1 (▷A), E4.6 (1QD)
unnamed: E4.8 (2QD), E5.5
unnamed: E4.13 (▷B), E5.3, E5.4
unnamed: E5.6, E5.9
unnamed: E5.10, E5.11
unnamed: E1.6, E13.1, E13.4
unnamed: E16.2 (D), E16.8 (~Q)
unnamed: E16.5 (Q), E16.12 (D)
unnamed: D17.11, E16.1 (~CLR), E16.13 (~CLR)
unnamed: E1.11, E16.4 (~PRE)
unnamed: E1.9, E16.9 (Q)
unnamed: E17.7 (A), E20.18 (B1), E21.9 (D0)
unnamed: E17.13 (B), E20.17 (B2), E21.10 (D1)
unnamed: E17.6 (C), E20.16 (B3), E21.11 (D2)
unnamed: E17.14 (D), E20.15 (B4), E21.13 (D3)
unnamed: E17.5 (E), E20.14 (B5), E21.14 (D4)
unnamed: E17.15 (F), E20.13 (B6), E21.15 (D5)
unnamed: E17.4 (G), E20.12 (B7), E21.16 (D6)
unnamed: E17.16 (H), E20.11 (B8), E21.17 (D7)
unnamed: E17.17 (QH), R16.1
unnamed: B22.3, B24.3, E17.1 (S0)
unnamed: B22.6, E17.19 (S1)
unnamed: B24.6, E20.19 (~G)
unnamed: E21.8 (A0), E23.7 (Y1)
unnamed: E21.7 (A1), E23.9 (Y2)
unnamed: E21.6 (A2), E23.12 (Y3)
unnamed: E21.5 (A3), E24.12 (Y3)
unnamed: E21.4 (A4), E24.9 (Y2)
unnamed: E21.3 (A5), E24.7 (Y1)
unnamed: E21.2 (A6), E24.4 (Y0)
unnamed: E21.1 (A7), E25.12 (Y3)
unnamed: E21.23 (A8), E25.9 (Y2)
unnamed: E21.22 (A9), E25.7 (Y1)
unnamed: E21.19 (A10), E25.4 (Y0)
unnamed: C20.10, E21.18 (~CE)
unnamed: C23.11, E25.3 (B0)
unnamed: F4.4 (1Y), RAM1.11 (A4), RAM2.11 (A4), RAM3.11 (A4), RAM4.11 (A4), RAM5.11 (A4), RAM6.11 (A4), RAM7.11 (A4), RAM8.11 (A4), RAM9.11 (A4), RAM10.11 (A4), RAM11.11 (A4), RAM12.11 (A4), RAM13.11 (A4), RAM14.11 (A4), RAM15.11 (A4), RAM16.11 (A4), RN5.4
unnamed: F4.7 (2Y), RAM1.10 (A5), RAM2.10 (A5), RAM3.10 (A5), RAM4.10 (A5), RAM5.10 (A5), RAM6.10 (A5), RAM7.10 (A5), RAM8.10 (A5), RAM9.10 (A5), RAM10.10 (A5), RAM11.10 (A5), RAM12.10 (A5), RAM13.10 (A5), RAM14.10 (A5), RAM15.10 (A5), RAM16.10 (A5), RN5.7
unnamed: F4.9 (3Y), RAM1.13 (A6), RAM2.13 (A6), RAM3.13 (A6), RAM4.13 (A6), RAM5.13 (A6), RAM6.13 (A6), RAM7.13 (A6), RAM8.13 (A6), RAM9.13 (A6), RAM10.13 (A6), RAM11.13 (A6), RAM12.13 (A6), RAM13.13 (A6), RAM14.13 (A6), RAM15.13 (A6), RAM16.13 (A6), RN5.2
unnamed: E5.8, F4.14 (4A)
unnamed: B1.8, F4.13 (4B)
unnamed: F4.12 (4Y), R49.2, RAM1.9 (A7), RAM2.9 (A7), RAM3.9 (A7), RAM4.9 (A7), RAM5.9 (A7), RAM6.9 (A7), RAM7.9 (A7), RAM8.9 (A7), RAM9.9 (A7), RAM10.9 (A7), RAM11.9 (A7), RAM12.9 (A7), RAM13.9 (A7), RAM14.9 (A7), RAM15.9 (A7), RAM16.9 (A7)
unnamed: D5.6, F4.1 (S), F5.1 (S)
unnamed: F5.4 (1Y), RAM1.5 (A0), RAM2.5 (A0), RAM3.5 (A0), RAM4.5 (A0), RAM5.5 (A0), RAM6.5 (A0), RAM7.5 (A0), RAM8.5 (A0), RAM9.5 (A0), RAM10.5 (A0), RAM11.5 (A0), RAM12.5 (A0), RAM13.5 (A0), RAM14.5 (A0), RAM15.5 (A0), RAM16.5 (A0), RN5.5
unnamed: F5.7 (2Y), RAM1.7 (A1), RAM2.7 (A1), RAM3.7 (A1), RAM4.7 (A1), RAM5.7 (A1), RAM6.7 (A1), RAM7.7 (A1), RAM8.7 (A1), RAM9.7 (A1), RAM10.7 (A1), RAM11.7 (A1), RAM12.7 (A1), RAM13.7 (A1), RAM14.7 (A1), RAM15.7 (A1), RAM16.7 (A1), RN5.8
unnamed: F5.9 (3Y), RAM1.6 (A2), RAM2.6 (A2), RAM3.6 (A2), RAM4.6 (A2), RAM5.6 (A2), RAM6.6 (A2), RAM7.6 (A2), RAM8.6 (A2), RAM9.6 (A2), RAM10.6 (A2), RAM11.6 (A2), RAM12.6 (A2), RAM13.6 (A2), RAM14.6 (A2), RAM15.6 (A2), RAM16.6 (A2), RN5.6
unnamed: F5.12 (4Y), RAM1.12 (A3), RAM2.12 (A3), RAM3.12 (A3), RAM4.12 (A3), RAM5.12 (A3), RAM6.12 (A3), RAM7.12 (A3), RAM8.12 (A3), RAM9.12 (A3), RAM10.12 (A3), RAM11.12 (A3), RAM12.12 (A3), RAM13.12 (A3), RAM14.12 (A3), RAM15.12 (A3), RAM16.12 (A3), RN5.3
unnamed: B11.8, FDC7.24 (CLK)
unnamed: A7.5, A10.5, FDC7.16 (DIREC)
unnamed: D17.9, FDC7.28 (HLD)
unnamed: B9.4, FDC7.35 (INDEX)
unnamed: C10.3, FDC7.32 (RDY)
unnamed: A7.1, A10.3, FDC7.15 (STEP)
unnamed: A10.9, FDC7.29 (TG43)
unnamed: A12.1, A12.13, E13.12, FDC7.30 (WG)
unnamed: A6.12, FDC7.36 (WPRT)
unnamed: A6.10, FDC7.34 (~TR00)
unnamed: J2.32, JP3.2
unnamed: JVIDEO1.1, R15.2
unnamed: Q1.1, R44.1, R45.2
unnamed: Q2.3, Q3.2, R4.2
unnamed: Q4.2, R6.2
unnamed: Q5.1, R12.1, R15.1
unnamed: Q5.2, Q6.1, R13.2, R16.2
unnamed: R27.2, R48.2
unnamed: R28.2, R47.2
unnamed: R37.2, R46.1, R46.2
unnamed: E13.6, RAM1.15 (~CAS), RAM2.15 (~CAS), RAM3.15 (~CAS), RAM4.15 (~CAS), RAM5.15 (~CAS), RAM6.15 (~CAS), RAM7.15 (~CAS), RAM8.15 (~CAS)
unnamed: D13.4, RAM1.3 (~WE), RAM2.3 (~WE), RAM3.3 (~WE), RAM4.3 (~WE), RAM5.3 (~WE), RAM6.3 (~WE), RAM7.3 (~WE), RAM8.3 (~WE), RAM9.3 (~WE), RAM10.3 (~WE), RAM11.3 (~WE), RAM12.3 (~WE), RAM13.3 (~WE), RAM14.3 (~WE), RAM15.3 (~WE), RAM16.3 (~WE)
unnamed: E13.3, RAM9.15 (~CAS), RAM10.15 (~CAS), RAM11.15 (~CAS), RAM12.15 (~CAS), RAM13.15 (~CAS), RAM14.15 (~CAS), RAM15.15 (~CAS), RAM16.15 (~CAS)
unnamed: D14.27 (0), RP11.2, RTC16.4 (A0)
unnamed: D14.28 (1), RP10.2, RTC16.5 (A1)
unnamed: D14.29 (2), RP9.2, RTC16.6 (A2)
unnamed: D14.30 (3), RP8.2, RTC16.7 (A3)
unnamed: D14.15 (0), RP4.2, RTC16.9 (D0)
unnamed: D14.14 (1), RP3.2, RTC16.10 (D1)
unnamed: D14.13 (2), RP2.2, RTC16.11 (D2)
unnamed: D14.12 (3), RP1.2, RTC16.12 (D3)
unnamed: RTC16.18 (HOLD), SW1.2
unnamed: D14.32 (5), RP6.2, RTC16.3 (READ)
unnamed: CAP4.1, Q4.1, R7.1, RTC16.1 (VCC)
unnamed: RTC16.2 (WRITE), SW1.4
unnamed: C64.1, RTC16.16 (XT), Y2.1
unnamed: C51.1, RTC16.17 (~XT), Y2.2
P: A1.2 (P0), A1.3 (Q0), A1.4 (P1), A1.5 (Q1), A1.6 (P2), A1.7 (Q2), A1.8 (P3), B4.6 (G1), B12.1 (~CLR), B12.4 (~PRE), B12.10 (~PRE), B12.13 (~CLR), B14.1 (~CLR), B14.11 (~PRE), B14.15 (~CLR), B20.1 (~CLR), B20.7 (ENP), B20.10 (ENT), B23.1 (~CLR), B25.3 (~K), B25.5 (~PRE), B25.11 (~PRE), B25.14 (J), B25.15 (~CLR), C4.6 (G1), C22.1 (~CLR), D9.3 (~CLR), D9.11 (~CLR), D10.4 (~PRE), D10.10 (~PRE), D10.13 (~CLR), D11.2 (D), D11.4 (~PRE), D11.10 (~PRE), D11.12 (D), D12.2 (D), D12.4 (~PRE), D12.10 (~PRE), D12.13 (~CLR), E2.4 (~PR), E2.10 (~PR), E16.10 (~PRE), E17.2 (~G1), E17.3 (~G2), E17.9 (~CLR), FDC7.23 (HLT)
P0: A2.16 (Q6), B3.1 (~G), B3.15 (~G), E25.2 (A0)
POC: A12.2, A12.12, B6.9, J7.30, Q3.3, R3.2, RTC16.8 (CS)
PS0: B15.11 (2A1), J7.31
PS1: B15.13 (2A2), J7.32
PS2: B15.15 (2A3), J7.33
PS3: B15.17 (2A4), J7.34
WIDE: A2.12 (Q4), A13.5
~2SIDED: B15.2 (1A1), J1.10, RN6.7
~4K_BANK: A1.19 (~P=Q), B1.3, B1.10, B1.11, C3.2 (A)
~6416: B3.7 (~Y3), C6.2, C24.13
~8024: C3.5 (~Y1), C6.1, C24.12
~A0: B14.3 (~K), B16.33 (C/~D)
~CHRA: C3.6 (~Y2), C6.12, C24.1
~CHRB: C3.7 (~Y3), C6.11, C24.2
~DNMI: B7.6, D3.3
~IN0: B4.15 (~Y0), B14.4 (CLK), B15.1 (~1G)
~IN1: B4.14 (~Y1), D17.1
~IN2: B4.13 (~Y2), B15.19 (~2G)
~IN3: B4.12 (~Y3), FDC7.4 (~RE)
~IN4: B4.11 (~Y4), J7.26
~IN5: B4.10 (~Y5), D17.13, J7.21
~IN6: B4.9 (~Y6), J7.23
~IN7: B4.7 (~Y7), D17.4
~MREQ: A1.1 (~G), B13.1, C1.19 (~MREQ)
~OUT0: B21.9, C4.15 (~Y0)
~OUT1: C4.14 (~Y1), D17.2
~OUT2: C4.13 (~Y2), J7.24
~OUT3: C4.12 (~Y3), FDC7.2 (~WE)
~OUT4: C4.11 (~Y4), J7.25
~OUT5: C4.10 (~Y5), J7.22
~OUT6: A21.1, A21.2, C4.9 (~Y6)
~OUT7: C4.7 (~Y7), D17.5
~RDKBD: B5.11, C6.4, J7.20
~RDROM: B5.8, C6.5, E12.15 (~CE)
~RD: A20.5, A23.9, B4.5 (~G2B), B5.10, B5.13, B6.12, B16.32 (~RD), C1.21 (~RD), C5.10, D13.5, D13.6, D14.35 (~RD), D20.1 (DIR), E20.1 (DIR)
~RESET: A2.1 (~CLR), A4.2 (1A1), B6.8, B16.21 (~RESET), C1.26 (~RESET), D6.1 (~CLR), FDC7.19 (~MR)
~RFSH: A1.9 (Q3), C1.28 (~RFSH), C6.6, E5.1, E5.2, E5.13
~RINT: B14.7 (~Q), D3.11
~RPI: A11.1 (CLK), A21.13, B6.10, C14.8 (D)
~RTC: A21.10, B7.2, B14.5 (~PRE), C25.12
~SINT: B16.5 (~INT), D3.10, RN1.5
~W0: B13.11, C3.12 (~Y0)
~W1: B13.13, C3.11 (~Y1)
~W2: C3.10 (~Y2), D6.11 (CLK), D13.2
~WAIT1: B14.14 (J), E1.8
Φ: A20.9, B22.2, B23.16 (Q6)
ΦBAUD: A23.1, B13.9, B23.4 (D1), R29.1
ΦBUFF: B14.10 (Q), B16.20 (CLK), D14.25 (Φ), R36.1
ΦZ: A4.15 (2A3), A13.9, B23.15 (Q5), B24.12, E2.3 (▷), E2.11 (▷), E16.3 (CLK), E16.11 (CLK)
Φ″: B11.4, B14.12 (CLK)
